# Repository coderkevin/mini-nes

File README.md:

# mini-nes
Support code for my version of a RPi-based Mini NES

This is based on/inspired by [DaftMike's NESPi](http://www.daftmike.com/2016/07/NESPi.html)
It is compatible with the 3D printed parts, but the hardware set up is simplified:

- No Arduino board needed, only the Raspberry Pi
- No power board support (In CPU shutdown, the RPi uses less power than the USB power supply you're using to power it)
- No fan support (buy good heatsinks, you likely won't miss the fan)

Here's a more detailed list of the features:

## Latching Power Button

The Power button is handled via GPIO and reset pin on the RPi.
The power button, when latched, brings the reset pin high, awakening the RPi from its shutdown.
After the RPi is powered up, a script is used on an output GPIO pin to hold the reset pin high in addition to the power button.
When the power button is unlatched, the GPIO holds the reset pin high until system shutdown completes.

## Power LED

The Power LED is connected to the reset pin, this indicates the true run state of the RPi. If the reset pin is high, the RPi is running. If the reset pin is low, then the RPi is held in reset and the CPU is in shutdown. It looks a little strange to see the power LED remain lit for a few seconds after unlatching the power button, but it is reassuring to know that the RPi isn't being subjected to a hard reset.

## Reset Button

The Reset button is connected to an RPi GPIO and simply does a system reboot.

## NFC Cartidge support

The NFC Reader is a PN532 running on the RPi's i2c interface. I've made a simple c interface to Python to utilize it. No Arduino or microcontroller needed to use it.

## No NFC tag writing needed

This system is designed to simply rely on the unique IDs already imprinted on your NFC tags. It uses a configuration file to map those UIDs to the correct game files to be run.

## Immediate loading of games

The system doesn't have to be powered off to start a game. It continually scans for cartridges and will restart Emulation Station as soon as a cart is installed. Don't worry if you like the feel of the old process though. You can still power off the system and install your cart and power it back on if you like.

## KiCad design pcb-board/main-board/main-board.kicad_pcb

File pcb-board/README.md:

# KiCad PCB projects
This are the Front and Main PCB projects designed on KiCad, this PCB is designed to be as easy to solder as possible using all through hole components. The NFC and
Front Panel connector are 1.25mm pitch and require careful soldering to avoid bridging solder points.

## BOM

This is the list of components and there respectable links to order each part from different suppliers:

Front Panel
- 150ohm Power LED Resistor, Quantity: 1 digikey: http://bit.ly/2qCImqK
- Front Panel Power LED, Quantity: 1 digikey: http://bit.ly/2qCURmf
- Latching Push Button Switche (Power Switch) Quantity: 1 amazon: http://amzn.to/2rpfMua
- Momentary Push Button Switch (Reset Switch) Quantity: 1 amazon: http://amzn.to/2rpqrF1

Main Board
- Micro JST Picoblade 1.25mm Pitch 4 Pin(NFC Reader) Quantity: 1 ebay: http://ebay.to/2sDfNLq
- Micro JST Picoblade 1.25mm Pitch 5 Pin(Front Control Panel) Quantity: 1 ebay: http://ebay.to/2sDwypP
- Resistor 10kohm, Quantity: 1 digikey: http://bit.ly/2rpp1KH
- 16 Pin Pi Header Connector, Quantity: 1 digikey: http://bit.ly/2rp8Ehp

## OSH Park Links
This PCB projects are publicly shared at oskpark.com you can order this boards from the following links:

-Front Panel PCB
https://oshpark.com/shared_projects/b4CEMlJS

-Main Board PCB
https://oshpark.com/shared_projects/rdgBPoq0

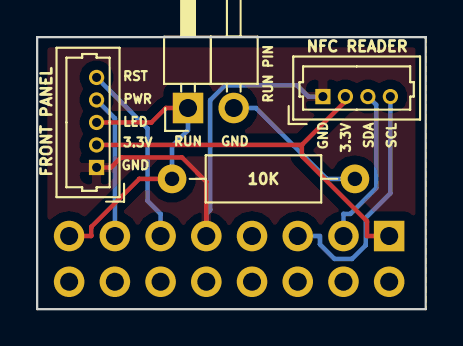
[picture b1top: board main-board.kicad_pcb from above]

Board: 2 copper layers, 21.6 x 15.1 mm, 5 parts (1 on the bottom side), 8 nets.

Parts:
10K: 10K; R_Axial_DIN0207_L6.3mm_D2.5mm_P10.16mm_Horizontal
FRONT PANEL: FRONT PANEL; Molex_PicoBlade_53047-0510_05x1.25mm_Straight
GPIO: RPi3 GPIO; Socket_Strip_Straight_2x08_Pitch2.54mm
NFC READER: NFC READER; Molex_PicoBlade_53047-0410_04x1.25mm_Straight
RUN PIN: RESET PIN; Pin_Header_Angled_1x02_Pitch2.54mm

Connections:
/GND: FRONT PANEL.1, GPIO.9, NFC READER.1
/LED: 10K.1, FRONT PANEL.3, GPIO.15, RUN PIN.1
/PWR: FRONT PANEL.4, GPIO.13
/RST: FRONT PANEL.5, GPIO.11
/SCL: GPIO.5, NFC READER.4
/SDA: GPIO.3, NFC READER.3
/VCC: FRONT PANEL.2, GPIO.1, NFC READER.2
unnamed: 10K.2, RUN PIN.2

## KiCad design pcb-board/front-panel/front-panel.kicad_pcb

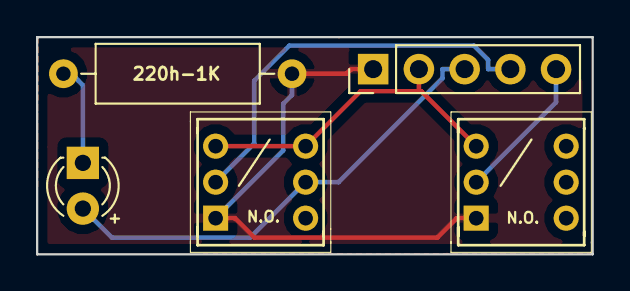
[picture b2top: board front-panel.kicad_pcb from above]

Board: 2 copper layers, 30.9 x 12.1 mm, 5 parts (0 on the bottom side), 6 nets.

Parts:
220h-1K: 220h; R_Axial_DIN0309_L9.0mm_D3.2mm_P12.70mm_Horizontal
J1: FRONT_CONN; Pin_Header_Straight_1x05_Pitch2.54mm
LED: LED; LED_D3.0mm
POWER: TL2230EE; TL2230
RESET: TL2230OA; TL2230

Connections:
/GND: 220h-1K.2, J1.1, POWER.1, RESET.1
/LED: J1.3, LED.2, POWER.5
/PWR: J1.4, POWER.2
/RST: J1.5, RESET.2
/VCC: J1.2, POWER.3, POWER.6, RESET.3
unnamed: 220h-1K.1, LED.1

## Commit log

2017-04-22 Add initial README info
2017-04-24 First edit of instructions
2017-04-24 Add C nfc support code
2017-04-24 nfc: Add base nfc init code
2017-04-24 nfc: Add UID copying
2017-04-24 Add nfc UID code (#1)
    * Add C nfc support code
    * nfc: Add base nfc init code
    * nfc: Add UID copying
2017-04-24 NFC: Add ctypes-based python module
2017-04-24 nfc: Add nfc_device type
2017-04-24 nfc: add polling
2017-04-27 Ignore .pyc files
2017-04-27 Corrections to polling
2017-04-27 Split out nfc logic to functions
    This splits out the nfc code to separate functions that will
    eventually be callable outside of the command-line application.
2017-04-30 Split nfc functions to their own file.
    In preparation for making a dynamically linked .so file, the nfc
    functionality has to be split out to a separate file from the main.
2017-04-30 Corrections for nfcutils
    Error code return for open.
    Add prefixes to nfcutils functions
2017-04-30 Makefile: create shared object
    This changes the makefile to make an nfcutils.so file.
    It uses it with the test program to ensure it works.
2017-04-30 Add continuous polling python script
2017-04-30 Add signal handler for continuous polling
2017-04-30 Make nfc_poll a daemon
2017-04-30 Use logging module in python for daemon
2017-04-30 Set group id of daemon
2017-05-01 Split out daemon into separate file
    Splits out daemon operation into seperate python file
    and adds init script
2017-05-13 Add /etc/nfc_poll/nfc_poll.conf
2017-05-13 Add cartridges to config
2017-05-14 Add lookup for cart uids
2017-05-14 Add emulator run command
2017-05-14 Split out rom manager into its own module.
2017-05-14 Adjust logger output.
2017-05-14 Update directions
2017-05-14 Add nes_buttons base class
2017-05-14 Add main for testing nes_buttons
2017-05-14 Add power sense to main loop
2017-05-14 Add halt/restart processing
2017-05-14 Add daemon for nes_buttons
2017-05-16 Add init enable for daemons
2017-05-17 Always copy to dirs for `make install`
2017-05-17 Always log NFC UID as it's read
2017-05-17 Update Directions with more detail on NFC.
2017-05-17 Add nes_buttons service install instructions
2017-05-17 Add wiring diagram
2017-05-17 Added more detail for the features supported.
2017-05-19 Add service start for nes_buttons
2017-05-22 Adjust rom script
    The rom script isn't quite working right. The joystick support
    disappears and there are permissions errors.
    This does the following:
    1. Run emulationstation.sh for the dashboard
    2. Runs the runcommand as user "pi" using bash instead of openvt
2017-05-23 Use sudo -u for runcommand
    Seems to work better as pi user
2017-05-24 Add screen manager
    This adds the beginnings of a screen manager script.
    This is designed to be run in /opt/retropie/config/all/autostart.sh
    It will handle the emulator and dashboard processes.
2017-05-24 Screen Manager: Add file watching
2017-05-24 Screen Manager: Minor cleanup
2017-05-24 Add makefile for screen_manager
2017-05-24 nfc_poll: use screen_manager
    This switches nfc_poll to use the screen_manager config
    file to start games and the dashboard.
2017-05-24 Move logs to /dev/shm
    This moves logs for nfc_poll and nes_buttons to /dev/shm
    This is where the rest of the RetroPie logs are, and it's in memory so
    it prevents the logs from thrashing the SD card.
2017-05-24 Add readme for screen_manager
2017-05-24 Updates to screen_manager readme
2017-05-24 Updates to Makefile/Directions
    Added installs of python-dev to each Makefile.
    Corrections to directions
    Added `screen_manager` install to directions.
2017-05-24 Make python-dev a prerequisite.
    I originally added this to `make install` but it's needed for make,
    so I just removed it and added it to the directions.
2017-05-24 Directions: remove "known issue"
2017-05-24 Remove rom_manager
    This removes the daftmike way of starting roms.
    It's no longer needed now that the screen_manager code is in and
    working.
2017-05-25 Update directions, no backslashes in roms
    The old directions told to escape spaces and parens with backslashes in
    the config file. This is no longer needed.
2017-05-25 nes_buttons: remove references to 'nes' user.
    I stopped using the nes user in this configuration, but there were a
    couple left-over places that referenced it.
2017-05-25 Add README for nes_buttons daemon
2017-05-25 Add troubleshooting guide
2017-05-27 Update DIRECTIONS.md
    Small updates
2017-05-30 Make nfc uid log to info instead of debug
2017-06-18 Add KiCad Front and Main PCB project files
2017-07-15 Update DIRECTIONS.md
    tiny fix to new file path
2017-07-17 Update DIRECTIONS.md (#6)
    tiny fix to new file path
2017-07-17 Add KiCad Front and Main PCB project files (#5)
2021-09-18 Add import for sys
    The error exit was failing because of a missing import.
2021-09-18 Add line in docs to fix issue with python-daemon
2021-09-23 Update Makefile
2021-09-28 Updated Directions
